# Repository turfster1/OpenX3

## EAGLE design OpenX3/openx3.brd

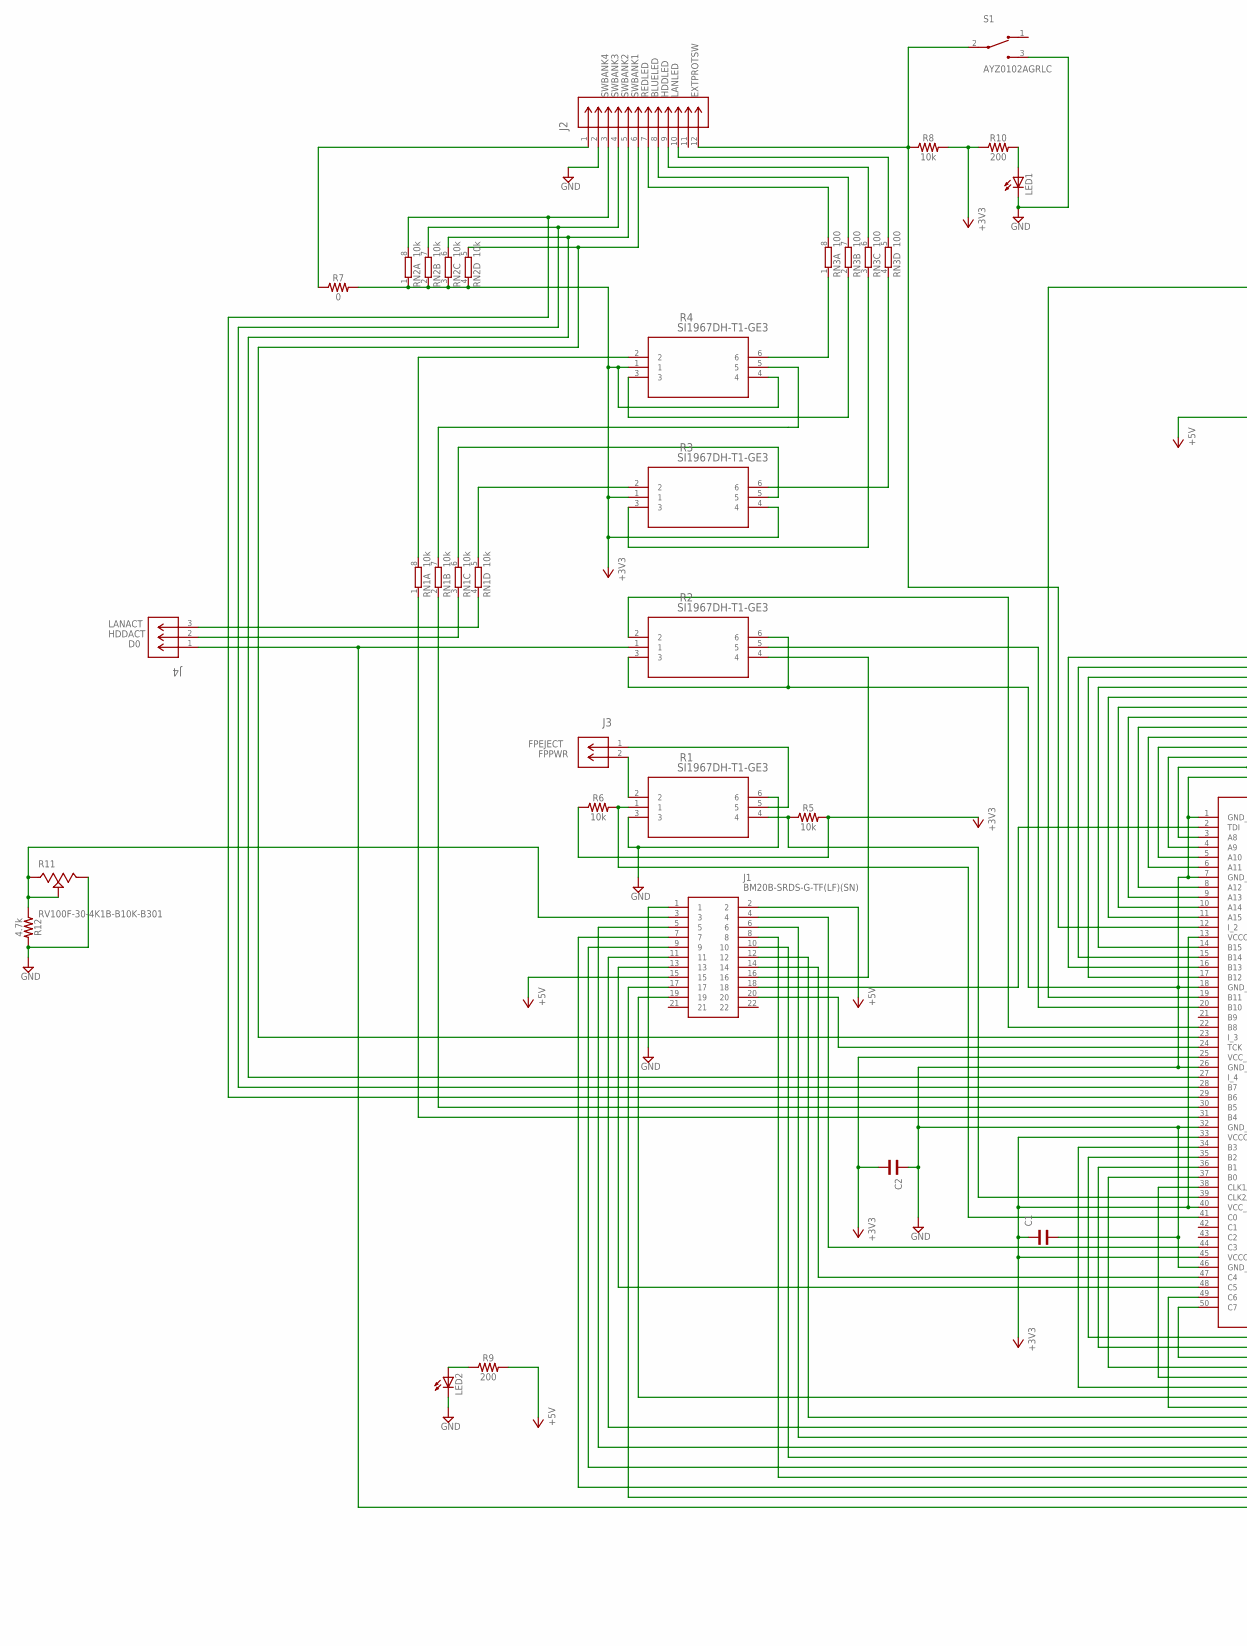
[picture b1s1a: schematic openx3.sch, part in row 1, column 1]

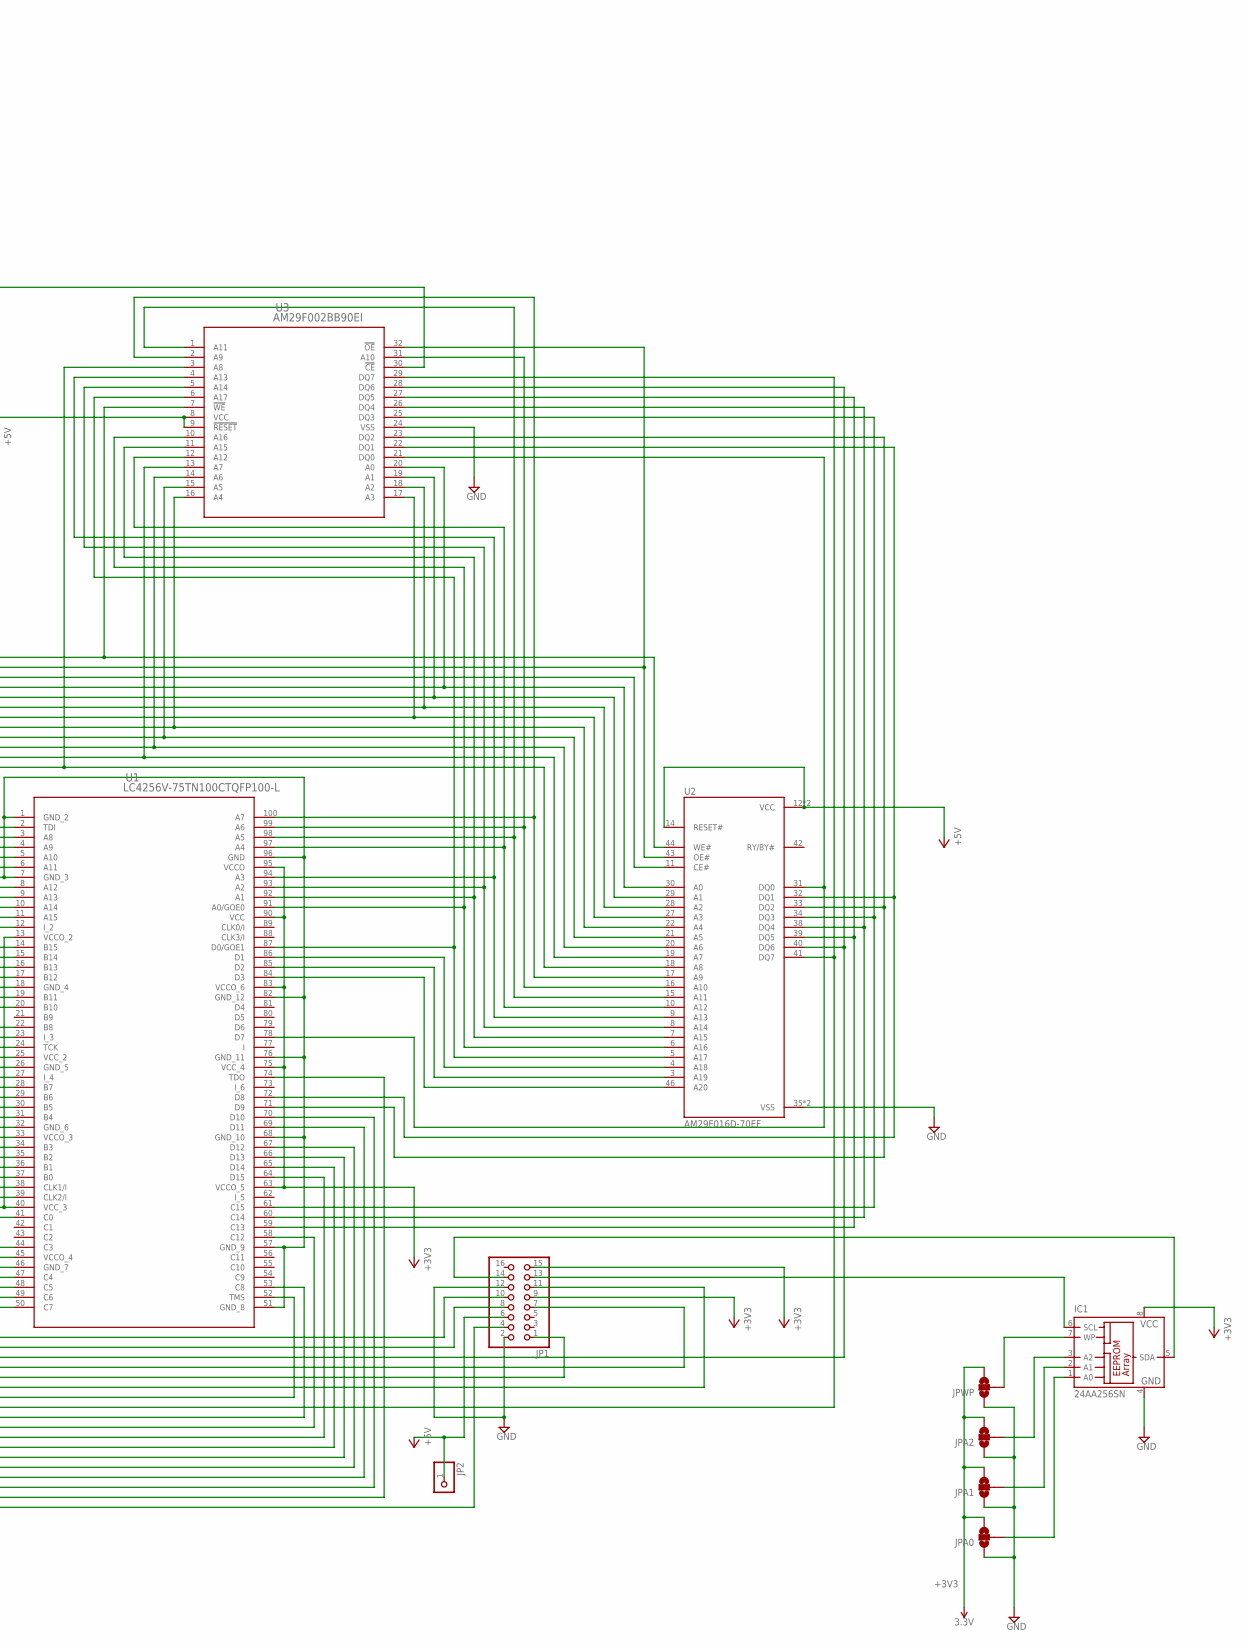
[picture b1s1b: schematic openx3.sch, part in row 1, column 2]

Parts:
C1, C2: WCAP-CSGP_0603_885012006001_REFLOW; WCAP-CSGP_0603_REFLOW
IC1: 24AA256SN; SO-08
J1: BM20B-SRDS-G-TF(LF)(SN); BM20BSRDSGTFLFSN
J2: SM12B-SRSS-TB(LF)(SN); CONN_SM12B-SRSS-TB(LF)(SN)
J3: 53398-0271; CON00327_2
J4: 1734260-3; CON3_1X3_DRM125_HPI
JP1: PINHD-2X8; 2X08
JP2: PINHD-1X1; 1X01
JPA0, JPA1, JPA2: JUMPER-SMT_3_NO_NO-SILK; SMT-JUMPER_3_NO_NO-SILK
JPWP: JUMPER-SMT_3_NO_NO-SILK; SMT-JUMPER_3_NO_NO-SILK
LED1, LED2: LEDCHIPLED_0805; CHIPLED_0805
R1, R2, R3, R4: SI1967DH-T1-GE3; TRANS_UM6J1-L
R5, R6, R8: 10k; 0603
R7: 0; 0603
R9, R10: 200; 0603
R11: RV100F-30-4K1B-B10K-B301; TRIM_RV100F-30-4K1B-B10K-B301
R12: 4.7k; 0603
RN1, RN2: 10k; 0603-ARV
RN3: 100; 0603-ARV
S1: AYZ0102AGRLC; SW_AYZ0102AGRLC
U1: LC4256V-75TN100CTQFP100-L; TQFP100-L
U2: AM29F016D-70EF; SOP50P2000X120-48N
U3: AM29F002BB90EI; TS032

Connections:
+3V3: C1.2, C2.1, IC1.8 (VCC), JP1.9, JP1.15, JPA0.3, JPA1.3, JPA2.3, JPWP.3, R3.1, R3.4, R4.1, R4.4, R5.2, R6.1, R7.2, R8.2, R10.1, RN2.1, RN2.2 (1), RN2.3 (1), RN2.4 (1), U1.13 (VCCO_2), U1.25 (VCC_2), U1.33 (VCCO_3), U1.40 (VCC_3), U1.45 (VCCO_4), U1.63 (VCCO_5), U1.75 (VCC_4), U1.83 (VCCO_6), U1.90 (VCC), U1.95 (VCCO)
+5V: J1.2, J1.15, JP1.6, JP2.1, R9.2, U2.12 (VCC), U2.14 (RESET#), U2.37 (VCC), U3.8 (VCC), U3.9 (!RESET)
A0: U1.14 (B15), U2.30 (A0), U3.20 (A0)
A1: U1.11 (A15), U2.29 (A1), U3.19 (A1)
A2: U1.10 (A14), U2.28 (A2), U3.18 (A2)
A3: U1.9 (A13), U2.27 (A3), U3.17 (A3)
A4: U1.8 (A12), U2.22 (A4), U3.16 (A4)
A5: U1.6 (A11), U2.21 (A5), U3.15 (A5)
A6: U1.5 (A10), U2.20 (A6), U3.14 (A6)
A7: U1.4 (A9), U2.19 (A7), U3.13 (A7)
A8: U1.3 (A8), U2.18 (A8), U3.3 (A8)
A9: U1.100 (A7), U2.17 (A9), U3.2 (A9)
A10: U1.99 (A6), U2.16 (A10), U3.31 (A10)
A11: U1.98 (A5), U2.15 (A11), U3.1 (A11)
A12: U1.97 (A4), U2.10 (A12), U3.12 (A12)
A13: U1.94 (A3), U2.9 (A13), U3.4 (A13)
A14: U1.93 (A2), U2.8 (A14), U3.5 (A14)
A15: U1.92 (A1), U2.7 (A15), U3.11 (A15)
A16: U1.91 (A0/GOE0), U2.6 (A16), U3.10 (A16)
A17: U1.87 (D0/GOE1), U2.5 (A17), U3.6 (A17)
A18: U1.86 (D1), U2.4 (A18)
A19: U1.85 (D2), U2.3 (A19)
A20: U1.84 (D3), U2.46 (A20)
BLUELED: J2.8, RN3.7 (2)
BUFLCE#: U1.19 (B11), U3.30 (!CE)
D0: J4.1, JP1.4, R2.1
DB0: J1.7, U1.70 (D10)
DB1: J1.8, U1.69 (D11)
DB2: J1.9, U1.67 (D12)
DB3: J1.10, U1.66 (D13)
DB4: J1.11, U1.58 (C12)
DB5: J1.12, U1.53 (C8)
DB6: J1.13, U1.48 (C5)
DB7: J1.14, U1.47 (C4)
DQ0: U1.78 (D7), U2.31 (DQ0), U3.21 (DQ0)
DQ1: U1.72 (D8), U2.32 (DQ1), U3.22 (DQ1)
DQ2: U1.71 (D9), U2.33 (DQ2), U3.23 (DQ2)
DQ3: U1.61 (C15), U2.34 (DQ3), U3.25 (DQ3)
DQ4: U1.60 (C14), U2.38 (DQ4), U3.26 (DQ4)
DQ5: U1.59 (C13), U2.39 (DQ5), U3.27 (DQ5)
DQ6: U1.50 (C7), U2.40 (DQ6), U3.28 (DQ6)
DQ7: U1.49 (C6), U2.41 (DQ7), U3.29 (DQ7)
E: J1.6, U1.64 (D15)
EPA0: IC1.1 (A0), JPA0.2
EPA1: IC1.2 (A1), JPA1.2
EPA2: IC1.3 (A2), JPA2.2
EPWP: IC1.7 (WP), JPWP.2
EXTPROTSW: J2.12, R8.1, S1.2, U1.12 (I_2)
FPEJECT: J3.1, R1.5
FPPWR: J3.2, R1.2
GND: C1.1, C2.2, IC1.4 (GND), J1.1, J2.2, JP1.2, JP1.12, JPA0.1, JPA1.1, JPA2.1, JPWP.1, LED1.C, LED2.C, R1.3, R1.6, R2.3, R2.6, R11.3, R12.2, S1.3, U1.1 (GND_2), U1.7 (GND_3), U1.18 (GND_4), U1.26 (GND_5), U1.32 (GND_6), U1.46 (GND_7), U1.51 (GND_8), U1.57 (GND_9), U1.68 (GND_10), U1.76 (GND_11), U1.82 (GND_12), U1.96 (GND), U2.35 (VSS), U2.36 (VSS), U3.24 (VSS)
HDDACT: J4.2, RN1.3 (1)
HDDLED: J2.9, RN3.6 (2)
K: J1.16, R2.4
LAD0: JP1.11, U1.34 (B3)
LAD1: JP1.10, U1.35 (B2)
LAD2: JP1.8, U1.36 (B1)
LAD3: JP1.7, U1.37 (B0)
LANACT: J4.3, RN1.4 (1)
LANLED: J2.10, RN3.5 (2)
LCLK: JP1.1, U1.38 (CLK1/I)
MNFLCE#: U1.17 (B12), U2.11 (CE#)
unnamed: LED2.A, R9.1
unnamed: R3.2, RN1.5 (2)
unnamed: R3.5, RN1.6 (2)
unnamed: LED1.A, R10.2
unnamed: R4.5, RN1.7 (2)
unnamed: R1.4, R5.1, U1.39 (CLK2/I)
unnamed: R1.1, R6.2, U1.41 (C0)
unnamed: R2.2, U1.22 (B8)
unnamed: R2.5, U1.20 (B10)
unnamed: R4.2, RN1.8 (2)
unnamed: R3.6, RN3.4 (1)
unnamed: R3.3, RN3.3 (1)
unnamed: R4.3, RN3.2 (1)
unnamed: R4.6, RN3.1
unnamed: RN1.1, U1.31 (B4)
unnamed: RN1.2 (1), U1.30 (B5)
unnamed: J2.1, R7.1
OE#: U1.15 (B14), U2.43 (OE#), U3.32 (!OE)
REDLED: J2.7, RN3.8 (2)
RS: J1.4, U1.44 (C3)
RW: J1.5, U1.65 (D14)
SCL: IC1.6 (SCL), JP1.13
SDA: IC1.5 (SDA), JP1.14
SWBANK1: J2.6, RN2.5 (2), U1.23 (I_3)
SWBANK2: J2.5, RN2.6 (2), U1.27 (I_4)
SWBANK3: J2.4, RN2.7 (2), U1.28 (B7)
SWBANK4: J2.3, RN2.8 (2), U1.29 (B6)
TCK: J1.20, U1.24 (TCK)
TDI: J1.18, U1.2 (TDI)
TDO: J1.17, U1.74 (TDO)
TMS: J1.19, U1.52 (TMS)
VO: J1.3, R11.1, R11.2, R12.1
WE#: U1.16 (B13), U2.44 (WE#), U3.7 (!WE)

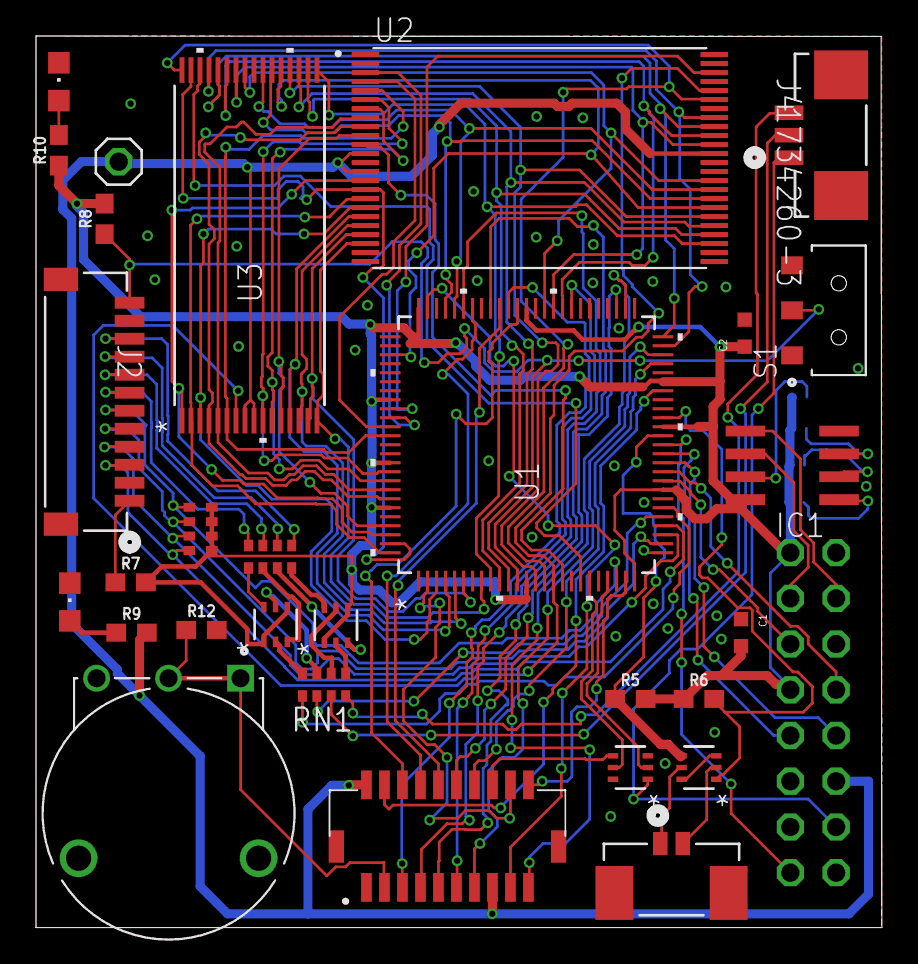
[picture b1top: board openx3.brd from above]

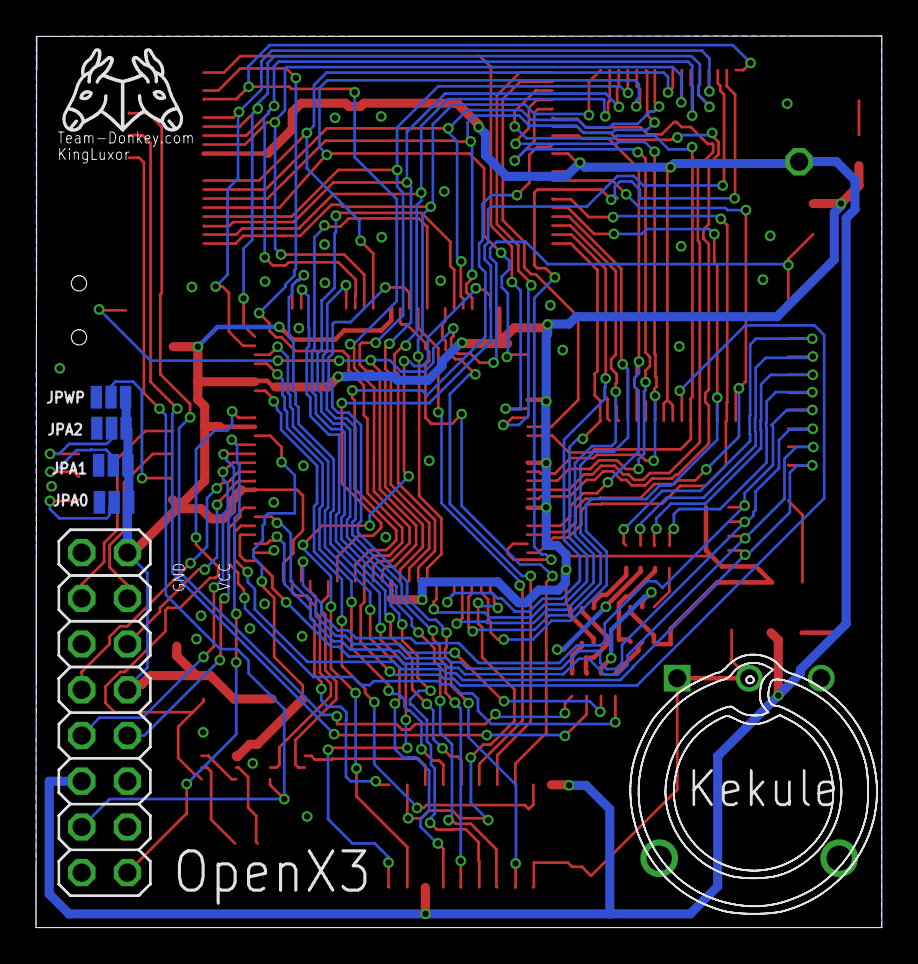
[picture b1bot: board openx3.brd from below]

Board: 2 copper layers, 47.0 x 49.5 mm, 35 parts (6 on the bottom side), 95 nets.

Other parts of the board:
U$1: KEKULE-0002

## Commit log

2020-02-05 more work
2020-02-18 first attempt at pcb layout - having trouble routing
2020-02-18 review ERC warnings; fix two missing junctions; one missing connection to GND on CPLD pin 18
2020-02-19 change lcd connector to vertical, remove lcd wire pads, correct connection for flash chips OE
2020-02-21 80% routed, fixes an issue on the LED resistor array
2020-02-21 x3 layer overlap image
2020-02-24 just have to fix airwires its detecting for some reason
2020-02-24 routing complete... passes DRC
2020-02-24 Add TD logo and text
2020-03-14 Make correction where resistor arrays were not connected to +3v3, previous net name was N$4 before connecting to +3v3
2020-03-14 Create dir
2020-03-14 intial commit
    starting with KalukeBlast code since it already has the LCD code and PWM started
2020-03-19 starting work on v2
    changes to use readily available components and better cpld pin assignment
2020-03-20 fixed missing ground connection to pins 3 and 6 of transistor array for front panel power and eject inputs
2020-04-01 minor fixes to traces, but no changes, adding gerber file for 2nd pcb order with fixed 3v3 and gnd
2020-04-07 added Research folder
2020-05-02 Updated part # for mosfet array from Nch to Pch, possible replacement is SI1967DH-T1-GE3 but still waiting to verify. Also fixed error in DRC that cause solder mask to be missing around some componen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

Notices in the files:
parts and their libraries:
Wurth_Elektronik_Passive_Capacitors_rev1: Copyright: Würth Elektronik
SparkFun-Jumpers: Licensing: Creative Commons ShareAlike 4.0 International - https://creativecommons.org/licenses/by-sa/4.0
COPYRIGHT: Copyright (C) 2018 Accelerated Designs. All rights reserved
